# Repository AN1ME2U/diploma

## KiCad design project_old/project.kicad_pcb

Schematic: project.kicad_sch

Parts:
C1, C9, C10, C18, C19, C20, C21, C22, C24, C25, C26, C27, C28, C29, C30: 0.1u; C_0603_1608Metric_Pad1.08x0.95mm_HandSolder
C2, C3, C11, C12: 10u; CP_EIA-6032-15_Kemet-U_Pad2.25x2.35mm_HandSolder
C4, C23: 0.001u; C_0603_1608Metric_Pad1.08x0.95mm_HandSolder
C5, C6, C14, C15: 22u; CP_EIA-6032-15_Kemet-U_Pad2.25x2.35mm_HandSolder
C7, C8, C16, C17: 0.1u; C_0805_2012Metric_Pad1.18x1.45mm_HandSolder
C13: 1u; C_0603_1608Metric_Pad1.08x0.95mm_HandSolder
D1: D; D_0805_2012Metric_Pad1.15x1.40mm_HandSolder
D2: LED; LED_0805_2012Metric_Pad1.15x1.40mm_HandSolder
J1: USB_C_Receptacle_USB2.0; USB_C_Receptacle_HRO_TYPE-C-31-M-12
J2: Conn_01x03; PinHeader_1x03_P2.54mm_Vertical
J3: USB_A; USB_A_Molex_67643_Horizontal
L1, L2, L3, L4: 220; L_2010_5025Metric_Pad1.52x2.65mm_HandSolder
R1, R3, R9: 1M; R_0603_1608Metric_Pad0.98x0.95mm_HandSolder
R2, R4, R5, R6: 4.7k; R_0603_1608Metric_Pad0.98x0.95mm_HandSolder
R7: 9.53; R_0603_1608Metric_Pad0.98x0.95mm_HandSolder
R8: 4K; R_0603_1608Metric_Pad0.98x0.95mm_HandSolder
R10: 24k9; R_0603_1608Metric_Pad0.98x0.95mm_HandSolder
U1: AMS1117-5.0; SOT-223-3_TabPin2
U2, U5: AMS1117-3.3; SOT-223-3_TabPin2
U3, U7: USBLC6-2P6; SOT-666
U4: AMS1117-1.5; SOT-223-3_TabPin2
U6: TUSB4041I; HTQFP-64-1EP_10x10mm_P0.5mm_EP8x8mm_Mask4.4x4.4mm_ThermalVi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
U8: TPS2560; VSON-10-1EP_3x3mm_P0.5mm_EP1.65x2.4mm
Y1: Crystal_GND23; Crystal_SMD_2520-4Pin_2.5x2.0mm

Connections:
1V1_pereph: C24.1, C25.1, C26.1, C27.1, C28.1, C29.1, C30.1, U6.19 (VDD), U6.25 (VDD), U6.37 (VDD), U6.45 (VDD), U6.53 (VDD), U6.60 (VDD), U6.63 (VDD)
1V2_pereph: L3.2
3V3_header: L2.2; also elsewhere on the board
3V3_pereph: C18.1, C19.1, C20.1, C22.1, L4.2, U6.2 (VDD33), U6.20 (VDD33), U6.31 (VDD33), U6.48 (VDD33); also elsewhere on the board
5V_header: L1.2; also elsewhere on the board
+5V: C2.1, C3.1, C11.1, C12.1, D1.1 (K), R8.1, U1.3 (VI), U2.3 (VI), U3.5 (VBUS), U4.3 (VI), U5.3 (VI), U6.16 (USB_VBUS), U8.2 (IN), U8.3 (IN); also elsewhere on the board
/USB_MAIN_N: J1.A7 (D-), J1.B7 (D-), U3.3 (I/O2)
/USB_MAIN_P: J1.A6 (D+), J1.B6 (D+), U3.1 (I/O1)
GND: C1.2, C2.2, C3.2, C4.2, C5.2, C6.2, C7.2, C8.2, C9.2, C10.2, C11.2, C12.2, C13.1, C14.2, C15.2, C16.2, C17.2, C18.2, C19.2, C20.2, C21.2, C22.2, C23.2, C24.2, C25.2, C26.2, C27.2, C28.2, C29.2, C30.2, D2.1 (K), J1.A1 (GND), J1.A12 (GND), J1.B1 (GND), J1.B12 (GND), J3.4 (GND), R1.2, R2.2, R4.2, R5.2, R6.2, R7.2, R9.2, R10.2, U1.1 (GND), U2.1 (GND), U3.2 (GND), U4.1 (GND), U5.1 (GND), U6.65 (VSS), U7.2 (GND), U8.1 (GND), Y1.2, Y1.4; also elsewhere on the board
unnamed: C1.1, C4.1, J1.S1 (SHIELD), R1.1
unnamed: C5.1, C7.1, L1.1, U1.2 (VO)
unnamed: C6.1, C8.1, L2.1, U2.2 (VO)
unnamed: C9.1, R3.1, U6.30 (XI), Y1.1
unnamed: C10.1, R3.2, U6.29 (XO), Y1.3
unnamed: C13.2, U6.18 (GRSTz)
unnamed: C14.1, C16.1, L3.1, U4.2 (VO)
unnamed: C15.1, C17.1, L4.1, U5.2 (VO)
unnamed: C21.1, C23.1, J3.5 (Shield), R9.1
unnamed: D1.2 (A), J1.A4 (VBUS), J1.A9 (VBUS), J1.B4 (VBUS), J1.B9 (VBUS)
unnamed: D2.2 (A), R8.2
unnamed: J2.1, U6.7 (SMBUSz)
unnamed: J2.2, U6.6 (SCL/SMBCLK)
unnamed: J2.3, U6.5 (SDA/SMBDAT)
unnamed: R2.1, U6.10 (GANGED/SMBA2/HS_UP)
unnamed: R4.1, U6.8 (FULLPWRMGMTz/SMBA1)
unnamed: R5.1, U6.13 (AUTOENz/HS_SUSPEND)
unnamed: R6.1, U6.17 (TEST)
unnamed: R7.1, U6.32 (USB_R1)
unnamed: R10.1, U8.7 (ILM)
unnamed: U3.4 (I/O2), U6.22 (USB_DM_UP)
unnamed: U3.6 (I/O1), U6.21 (USB_DP_UP)
USB1_DN: U6.34 (USB_DM_DN1); also elsewhere on the board
USB1_DP: U6.33 (USB_DP_DN1); also elsewhere on the board
USB2_DN: U6.42 (USB_DM_DN2); also elsewhere on the board
USB2_DP: U6.41 (USB_DP_DN2); also elsewhere on the board
USB3_DN: U6.50 (USB_DM_DN3); also elsewhere on the board
USB3_DP: U6.49 (USB_DP_DN3); also elsewhere on the board
USB4_DN: J3.2 (D-), U6.57 (USB_DM_DN4), U7.1 (I/O1), U7.6 (I/O1)
USB4_DP: J3.3 (D+), U6.56 (USB_DP_DN4), U7.3 (I/O2), U7.4 (I/O2)
USB4_VBUS: J3.1 (VBUS), U7.5 (VBUS), U8.9 (OUT1)
USB_OTG_VBUS: U8.8 (OUT2); also elsewhere on the board

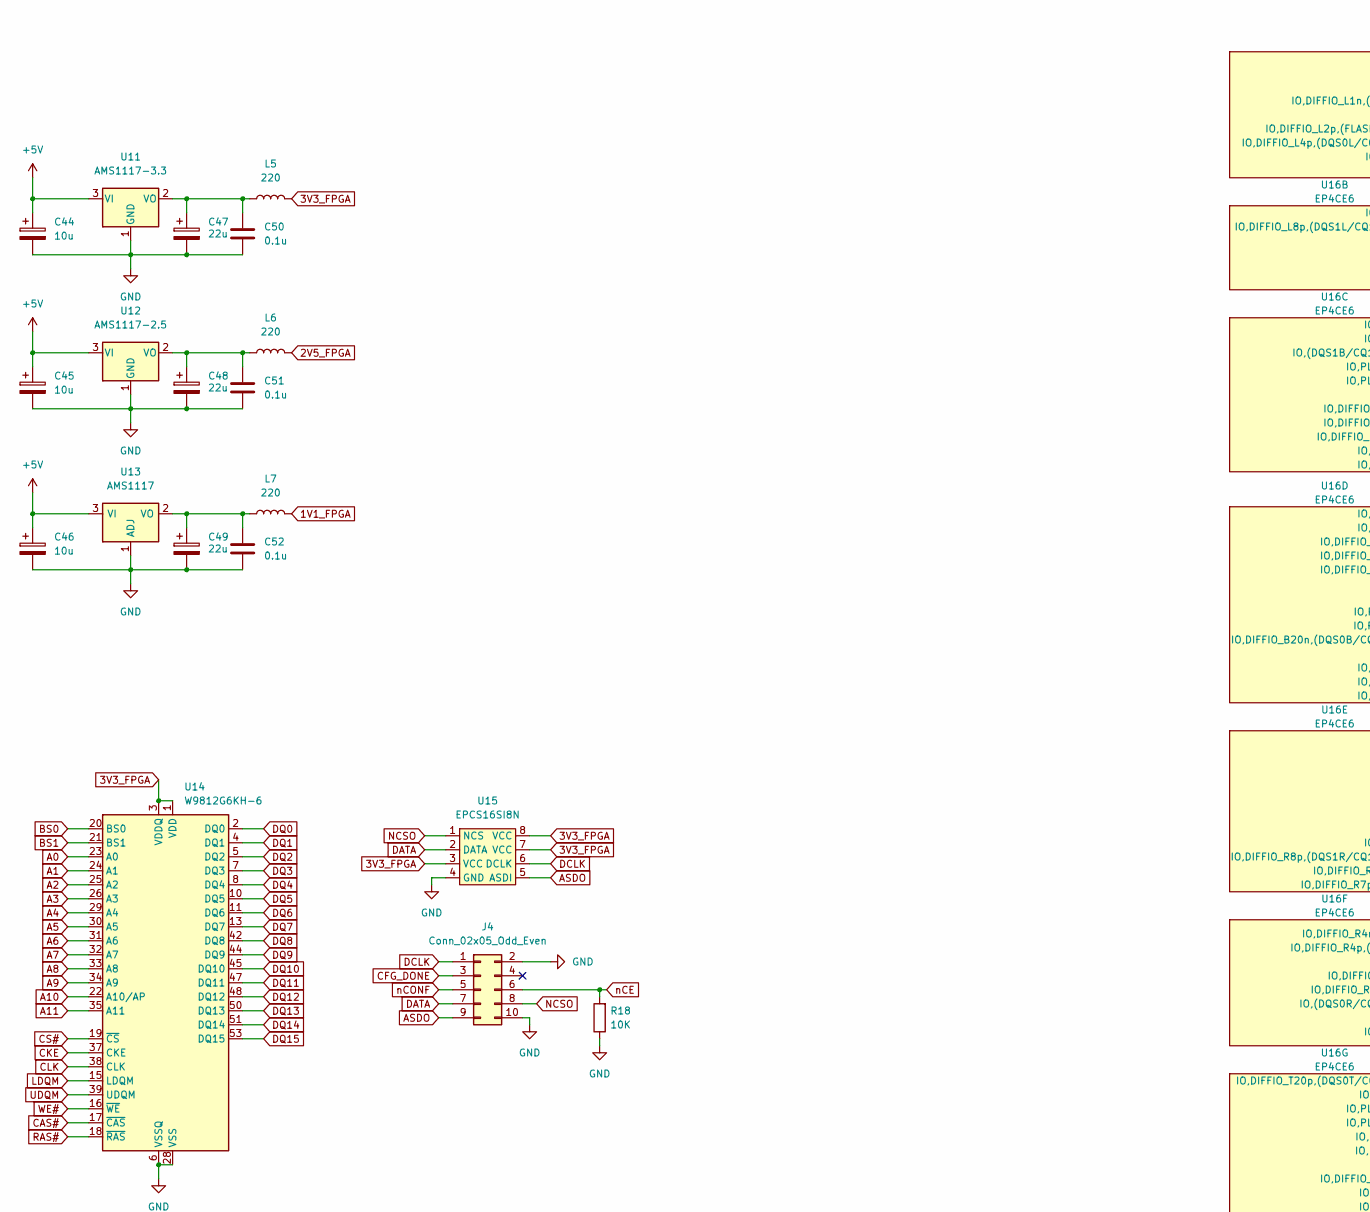
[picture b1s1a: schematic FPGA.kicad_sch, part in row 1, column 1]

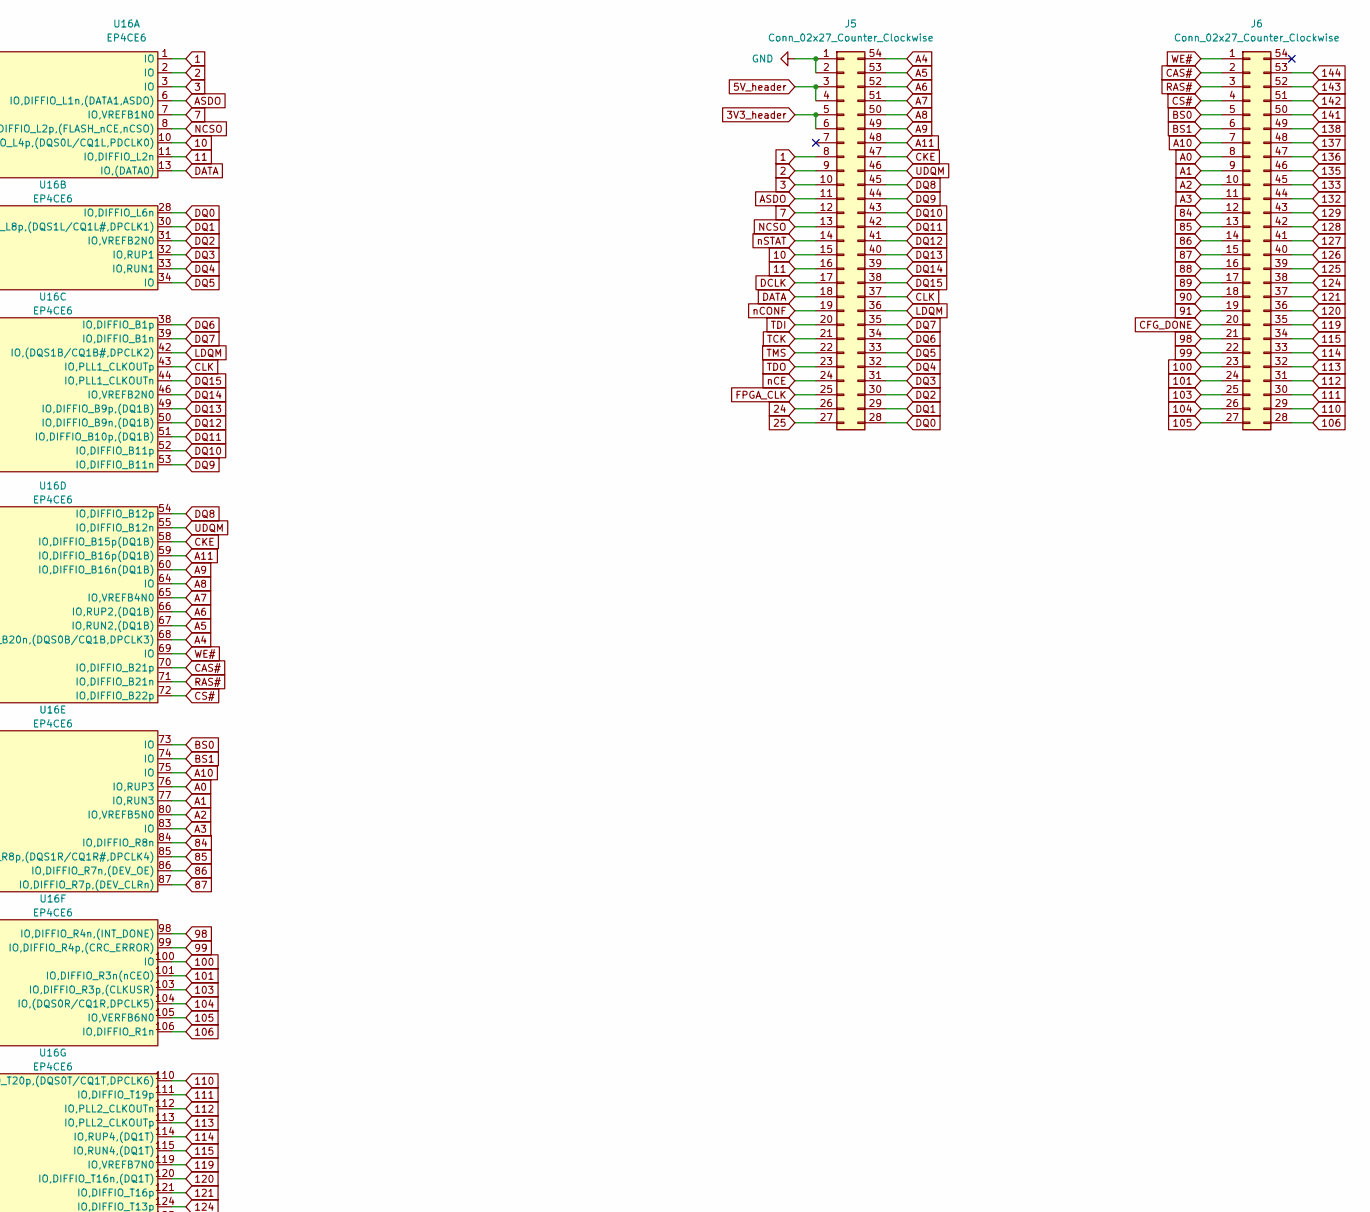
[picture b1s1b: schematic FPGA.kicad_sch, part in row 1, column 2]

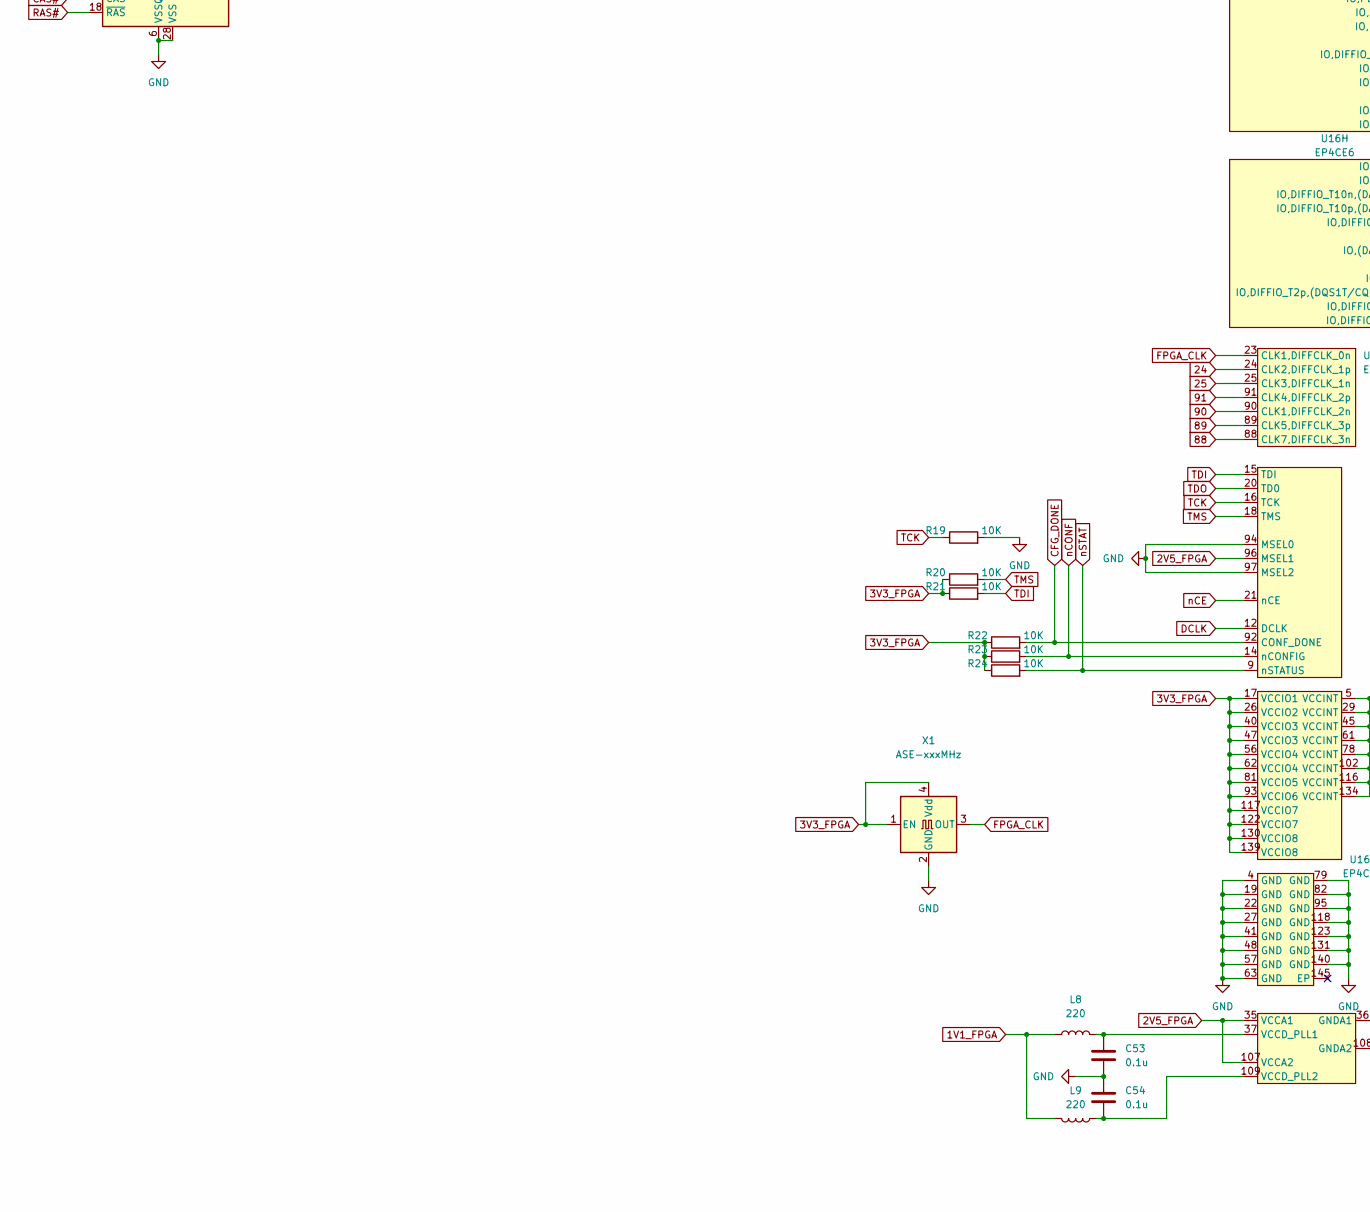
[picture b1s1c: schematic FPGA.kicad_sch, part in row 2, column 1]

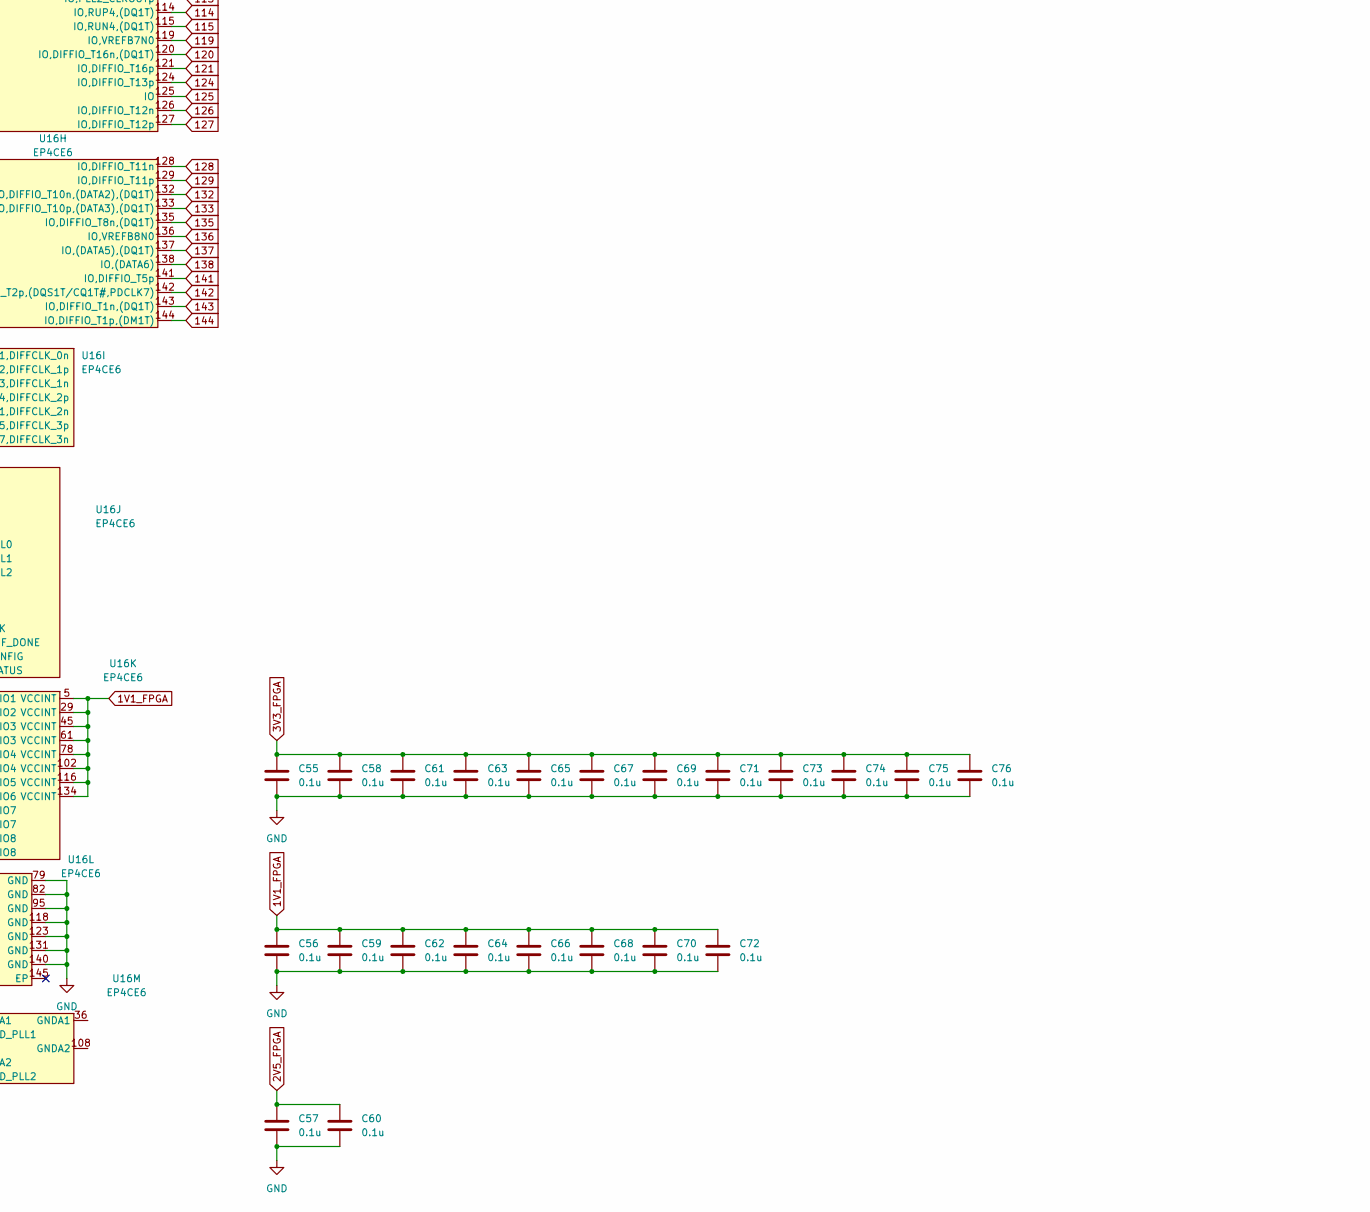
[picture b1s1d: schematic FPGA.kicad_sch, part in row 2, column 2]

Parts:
C44, C45, C46: 10u; CP_EIA-6032-15_Kemet-U_Pad2.25x2.35mm_HandSolder
C47, C48, C49: 22u; CP_EIA-6032-15_Kemet-U_Pad2.25x2.35mm_HandSolder
C50, C51, C52: 0.1u; C_0805_2012Metric_Pad1.18x1.45mm_HandSolder
C53, C54, C55, C56, C57, C58, C59, C60, C61, C62, C63, C64, C65, C66, C67, C68, C69, C70, C71, C72, C73, C74, C75, C76: 0.1u; C_0603_1608Metric_Pad1.08x0.95mm_HandSolder
J4: Conn_02x05_Odd_Even; PinHeader_2x05_P2.54mm_Vertical
J5, J6: Conn_02x27_Counter_Clockwise; PinHeader_2x27_P2.54mm_Vertical
L5, L6, L7, L8, L9: 220; L_2010_5025Metric_Pad1.52x2.65mm_HandSolder
R18, R19, R20, R21, R22, R23, R24: 10K; R_0603_1608Metric_Pad0.98x0.95mm_HandSolder
U11: AMS1117-3.3; SOT-223-3_TabPin2
U12: AMS1117-2.5; SOT-223-3_TabPin2
U13: AMS1117; SOT-223-3_TabPin2
U14: W9812G6KH-6; TSOP-II-54_22.2x10.16mm_P0.8mm
U15: EPCS16SI8N; SOIC-8-1EP_3.9x4.9mm_P1.27mm_EP2.29x3mm
U16: EP4CE6; TQFP-144_20x20mm_P0.5mm
X1: ASE-xxxMHz; Oscillator_SMD_Abracon_ASE-4Pin_3.2x2.5mm

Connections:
1: J5.8, U16.1 (IO)
1V1_FPGA: C56.1, C59.1, C62.1, C64.1, C66.1, C68.1, C70.1, C72.1, L7.2, L8.1, L9.2, U16.5 (VCCINT), U16.29 (VCCINT), U16.45 (VCCINT), U16.61 (VCCINT), U16.78 (VCCINT), U16.102 (VCCINT), U16.116 (VCCINT), U16.134 (VCCINT)
2: J5.9, U16.2 (IO)
2V5_FPGA: C57.1, C60.1, L6.2, U16.35 (VCCA1), U16.96 (MSEL1), U16.107 (VCCA2)
3: J5.10, U16.3 (IO)
3V3_FPGA: C55.1, C58.1, C61.1, C63.1, C65.1, C67.1, C69.1, C71.1, C73.1, C74.1, C75.1, C76.1, L5.2, R20.1, R21.1, R22.1, R23.1, R24.1, U14.1 (VDD), U14.3 (VDDQ), U14.9 (VDDQ), U14.14 (VDD), U14.27 (VDD), U14.43 (VDDQ), U14.49 (VDDQ), U15.3 (VCC), U15.7 (VCC), U15.8 (VCC), U16.17 (VCCIO1), U16.26 (VCCIO2), U16.40 (VCCIO3), U16.47 (VCCIO3), U16.56 (VCCIO4), U16.62 (VCCIO4), U16.81 (VCCIO5), U16.93 (VCCIO6), U16.117 (VCCIO7), U16.122 (VCCIO7), U16.130 (VCCIO8), U16.139 (VCCIO8), X1.1 (EN), X1.4 (Vdd)
3V3_header: J5.5, J5.6; also elsewhere on the board
5V_header: J5.3, J5.4; also elsewhere on the board
7: J5.12, U16.7 (IO,VREFB1N0)
10: J5.15, U16.10 (IO,DIFFIO_L4p,(DQS0L/CQ1L,PDCLK0))
11: J5.16, U16.11 (IO,DIFFIO_L2n)
24: J5.26, U16.24 (CLK2,DIFFCLK_1p)
25: J5.27, U16.25 (CLK3,DIFFCLK_1n)
84: J6.12, U16.84 (IO,DIFFIO_R8n)
85: J6.13, U16.85 (IO,DIFFIO_R8p,(DQS1R/CQ1R#,DPCLK4))
86: J6.14, U16.86 (IO,DIFFIO_R7n,(DEV_OE))
87: J6.15, U16.87 (IO,DIFFIO_R7p,(DEV_CLRn))
88: J6.16, U16.88 (CLK7,DIFFCLK_3n)
89: J6.17, U16.89 (CLK5,DIFFCLK_3p)
90: J6.18, U16.90 (CLK1,DIFFCLK_2n)
91: J6.19, U16.91 (CLK4,DIFFCLK_2p)
98: J6.21, U16.98 (IO,DIFFIO_R4n,(INT_DONE))
99: J6.22, U16.99 (IO,DIFFIO_R4p,(CRC_ERROR))
100: J6.23, U16.100 (IO)
101: J6.24, U16.101 (IO,DIFFIO_R3n(nCEO))
103: J6.25, U16.103 (IO,DIFFIO_R3p,(CLKUSR))
104: J6.26, U16.104 (IO,(DQS0R/CQ1R,DPCLK5))
105: J6.27, U16.105 (IO,VERFB6N0)
106: J6.28, U16.106 (IO,DIFFIO_R1n)
110: J6.29, U16.110 (IO,DIFFIO_T20p,(DQS0T/CQ1T,DPCLK6))
111: J6.30, U16.111 (IO,DIFFIO_T19p)
112: J6.31, U16.112 (IO,PLL2_CLKOUTn)
113: J6.32, U16.113 (IO,PLL2_CLKOUTp)
114: J6.33, U16.114 (IO,RUP4,(DQ1T))
115: J6.34, U16.115 (IO,RUN4,(DQ1T))
119: J6.35, U16.119 (IO,VREFB7N0)
120: J6.36, U16.120 (IO,DIFFIO_T16n,(DQ1T))
121: J6.37, U16.121 (IO,DIFFIO_T16p)
124: J6.38, U16.124 (IO,DIFFIO_T13p)
125: J6.39, U16.125 (IO)
126: J6.40, U16.126 (IO,DIFFIO_T12n)
127: J6.41, U16.127 (IO,DIFFIO_T12p)
128: J6.42, U16.128 (IO,DIFFIO_T11n)
129: J6.43, U16.129 (IO,DIFFIO_T11p)
132: J6.44, U16.132 (IO,DIFFIO_T10n,(DATA2),(DQ1T))
133: J6.45, U16.133 (IO,DIFFIO_T10p,(DATA3),(DQ1T))
135: J6.46, U16.135 (IO,DIFFIO_T8n,(DQ1T))
136: J6.47, U16.136 (IO,VREFB8N0)
137: J6.48, U16.137 (IO,(DATA5),(DQ1T))
138: J6.49, U16.138 (IO,(DATA6))
141: J6.50, U16.141 (IO,DIFFIO_T5p)
142: J6.51, U16.142 (IO,DIFFIO_T2p,(DQS1T/CQ1T#,PDCLK7))
143: J6.52, U16.143 (IO,DIFFIO_T1n,(DQ1T))
144: J6.53, U16.144 (IO,DIFFIO_T1p,(DM1T))
+5V: C44.1, C45.1, C46.1, U11.3 (VI), U12.3 (VI), U13.3 (VI); also elsewhere on the board
A0: J6.8, U14.23 (A0), U16.76 (IO,RUP3)
A1: J6.9, U14.24 (A1), U16.77 (IO,RUN3)
A2: J6.10, U14.25 (A2), U16.80 (IO,VREFB5N0)
A3: J6.11, U14.26 (A3), U16.83 (IO)
A4: J5.54, U14.29 (A4), U16.68 (IO,DIFFIO_B20n,(DQS0B/CQ1B,DPCLK3))
A5: J5.53, U14.30 (A5), U16.67 (IO,RUN2,(DQ1B))
A6: J5.52, U14.31 (A6), U16.66 (IO,RUP2,(DQ1B))
A7: J5.51, U14.32 (A7), U16.65 (IO,VREFB4N0)
A8: J5.50, U14.33 (A8), U16.64 (IO)
A9: J5.49, U14.34 (A9), U16.60 (IO,DIFFIO_B16n(DQ1B))
A10: J6.7, U14.22 (A10/AP), U16.75 (IO)
A11: J5.48, U14.35 (A11), U16.59 (IO,DIFFIO_B16p(DQ1B))
ASDO: J4.9, J5.11, U15.5 (ASDI), U16.6 (IO,DIFFIO_L1n,(DATA1,ASDO))
BS0: J6.5, U14.20 (BS0), U16.73 (IO)
BS1: J6.6, U14.21 (BS1), U16.74 (IO)
CAS#: J6.2, U14.17 (~CAS), U16.70 (IO,DIFFIO_B21p)
CFG_DONE: J4.3, J6.20, R22.2, U16.92 (CONF_DONE)
CKE: J5.47, U14.37 (CKE), U16.58 (IO,DIFFIO_B15p(DQ1B))
CLK: J5.37, U14.38 (CLK), U16.43 (IO,PLL1_CLKOUTp)
CS#: J6.4, U14.19 (~CS), U16.72 (IO,DIFFIO_B22p)
DATA: J4.7, J5.18, U15.2 (DATA), U16.13 (IO,(DATA0))
DCLK: J4.1, J5.17, U15.6 (DCLK), U16.12 (DCLK)
DQ0: J5.28, U14.2 (DQ0), U16.28 (IO,DIFFIO_L6n)
DQ1: J5.29, U14.4 (DQ1), U16.30 (IO,DIFFIO_L8p,(DQS1L/CQ1L#,DPCLK1))
DQ2: J5.30, U14.5 (DQ2), U16.31 (IO,VREFB2N0)
DQ3: J5.31, U14.7 (DQ3), U16.32 (IO,RUP1)
DQ4: J5.32, U14.8 (DQ4), U16.33 (IO,RUN1)
DQ5: J5.33, U14.10 (DQ5), U16.34 (IO)
DQ6: J5.34, U14.11 (DQ6), U16.38 (IO,DIFFIO_B1p)
DQ7: J5.35, U14.13 (DQ7), U16.39 (IO,DIFFIO_B1n)
DQ8: J5.45, U14.42 (DQ8), U16.54 (IO,DIFFIO_B12p)
DQ9: J5.44, U14.44 (DQ9), U16.53 (IO,DIFFIO_B11n)
DQ10: J5.43, U14.45 (DQ10), U16.52 (IO,DIFFIO_B11p)
DQ11: J5.42, U14.47 (DQ11), U16.51 (IO,DIFFIO_B10p,(DQ1B))
DQ12: J5.41, U14.48 (DQ12), U16.50 (IO,DIFFIO_B9n,(DQ1B))
DQ13: J5.40, U14.50 (DQ13), U16.49 (IO,DIFFIO_B9p,(DQ1B))
DQ14: J5.39, U14.51 (DQ14), U16.46 (IO,VREFB2N0)
DQ15: J5.38, U14.53 (DQ15), U16.44 (IO,PLL1_CLKOUTn)
FPGA_CLK: J5.25, U16.23 (CLK1,DIFFCLK_0n), X1.3 (OUT)
GND: C44.2, C45.2, C46.2, C47.2, C48.2, C49.2, C50.2, C51.2, C52.2, C53.2, C54.1, C55.2, C56.2, C57.2, C58.2, C59.2, C60.2, C61.2, C62.2, C63.2, C64.2, C65.2, C66.2, C67.2, C68.2, C69.2, C70.2, C71.2, C72.2, C73.2, C74.2, C75.2, C76.2, J4.2, J4.10, J5.1, J5.2, R18.1, R19.2, U11.1 (GND), U12.1 (GND), U13.1 (ADJ), U14.6 (VSSQ), U14.12 (VSSQ), U14.28 (VSS), U14.41 (VSS), U14.46 (VSSQ), U14.52 (VSSQ), U14.54 (VSS), U15.4 (GND), U16.4 (GND), U16.19 (GND), U16.22 (GND), U16.27 (GND), U16.41 (GND), U16.48 (GND), U16.57 (GND), U16.63 (GND), U16.79 (GND), U16.82 (GND), U16.94 (MSEL0), U16.95 (GND), U16.97 (MSEL2), U16.118 (GND), U16.123 (GND), U16.131 (GND), U16.140 (GND), X1.2 (GND); also elsewhere on the board
LDQM: J5.36, U14.15 (LDQM), U16.42 (IO,(DQS1B/CQ1B#,DPCLK2))
NCSO: J4.8, J5.13, U15.1 (NCS), U16.8 (IO,DIFFIO_L2p,(FLASH_nCE,nCSO))
unnamed: C47.1, C50.1, L5.1, U11.2 (VO)
unnamed: C48.1, C51.1, L6.1, U12.2 (VO)
unnamed: C49.1, C52.1, L7.1, U13.2 (VO)
unnamed: C53.1, L8.2, U16.37 (VCCD_PLL1)
unnamed: C54.2, L9.1, U16.109 (VCCD_PLL2)
RAS#: J6.3, U14.18 (~RAS), U16.71 (IO,DIFFIO_B21n)
TCK: J5.21, R19.1, U16.16 (TCK)
TDI: J5.20, R21.2, U16.15 (TDI)
TDO: J5.23, U16.20 (TD0)
TMS: J5.22, R20.2, U16.18 (TMS)
UDQM: J5.46, U14.39 (UDQM), U16.55 (IO,DIFFIO_B12n)
WE#: J6.1, U14.16 (~WE), U16.69 (IO)
nCE: J4.6, J5.24, R18.2, U16.21 (nCE)
nCONF: J4.5, J5.19, R23.2, U16.14 (nCONFIG)
nSTAT: J5.14, R24.2, U16.9 (nSTATUS)

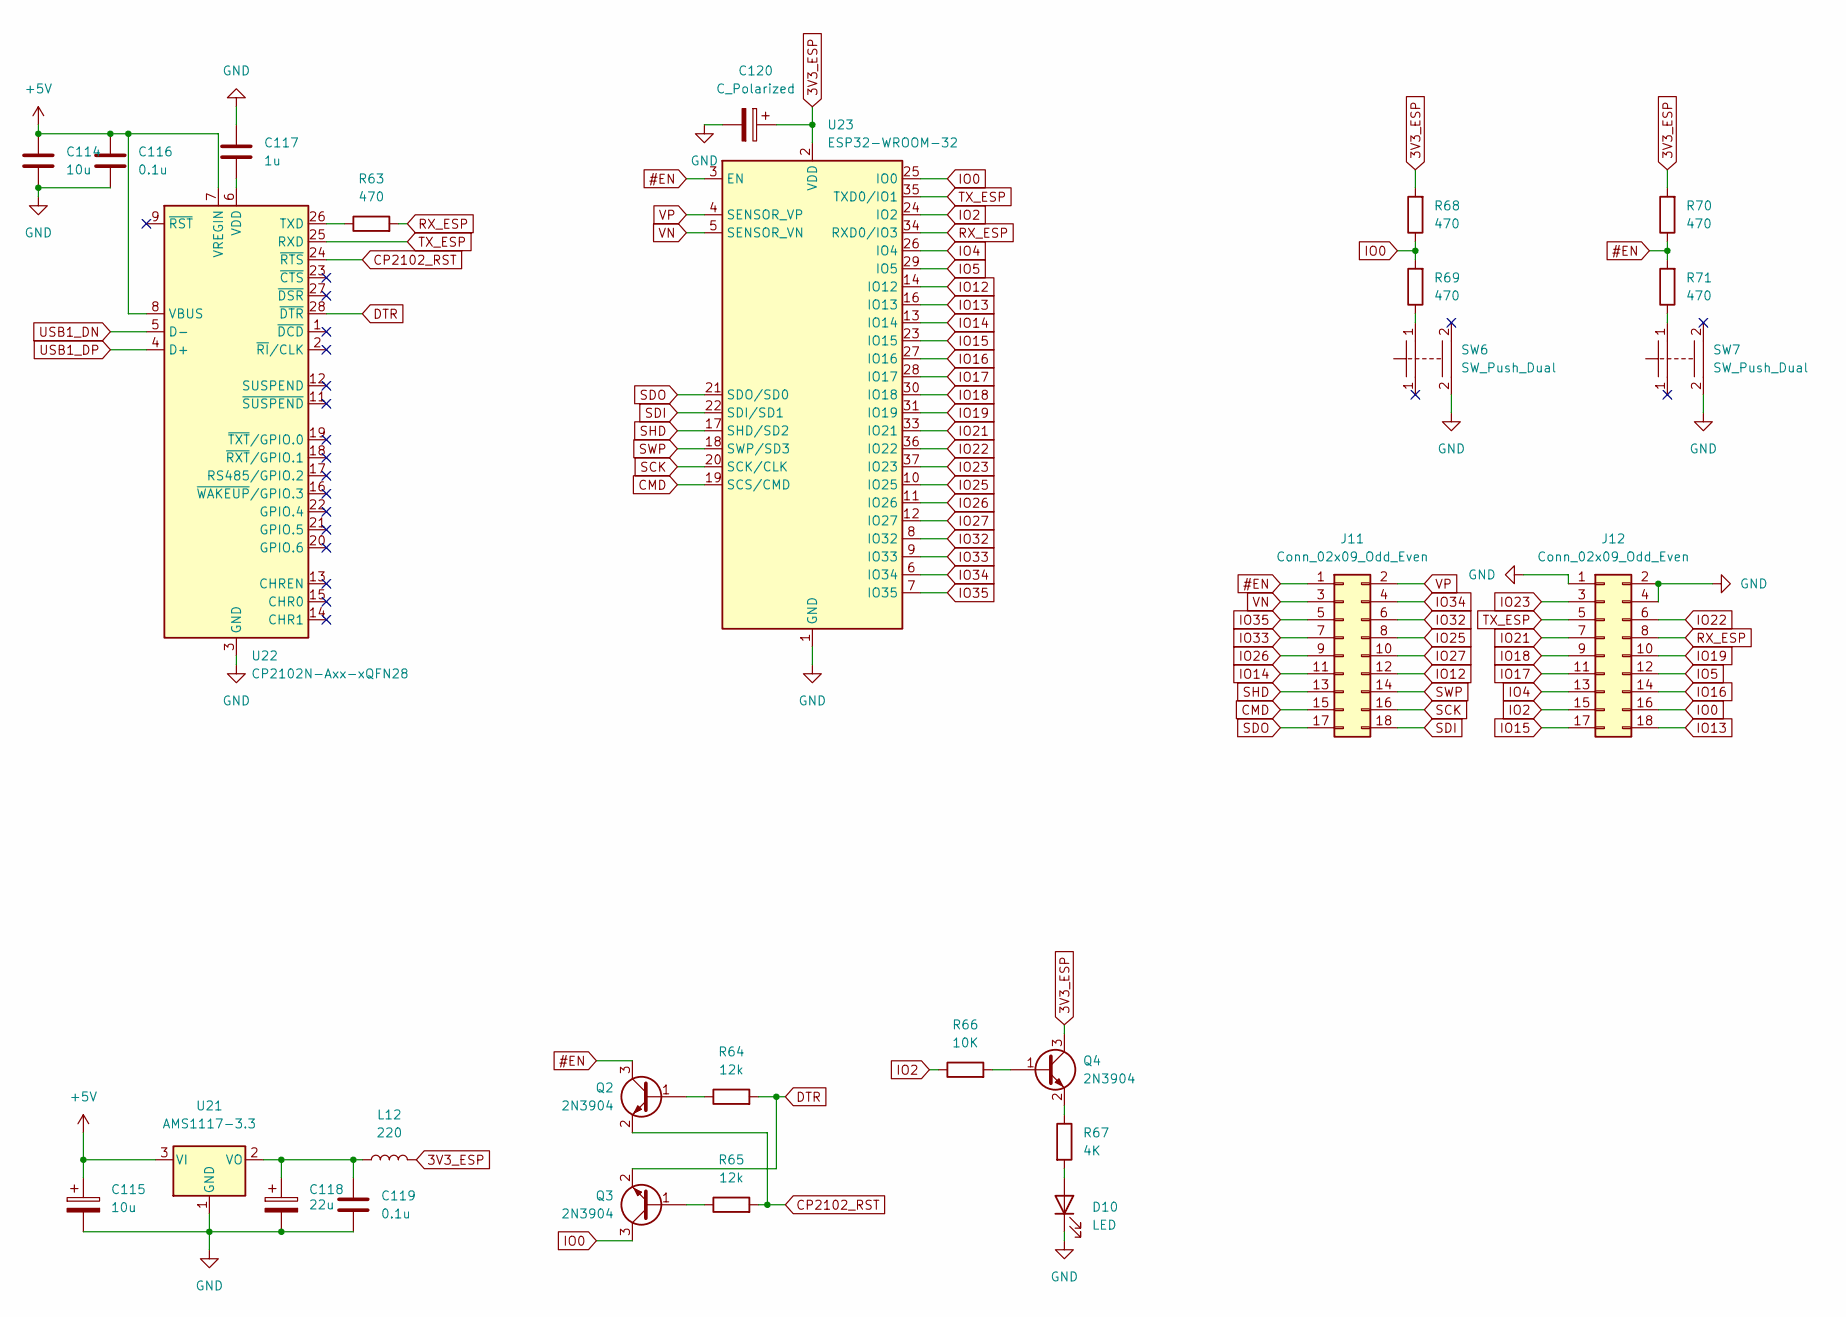
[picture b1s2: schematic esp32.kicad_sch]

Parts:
C114: 10u; C_0603_1608Metric_Pad1.08x0.95mm_HandSolder
C115: 10u; CP_EIA-6032-15_Kemet-U_Pad2.25x2.35mm_HandSolder
C116: 0.1u; C_0603_1608Metric_Pad1.08x0.95mm_HandSolder
C117: 1u; C_0603_1608Metric_Pad1.08x0.95mm_HandSolder
C118: 22u; CP_EIA-6032-15_Kemet-U_Pad2.25x2.35mm_HandSolder
C119: 0.1u; C_0805_2012Metric_Pad1.18x1.45mm_HandSolder
C120: C_Polarized; CP_EIA-1608-08_AVX-J_Pad1.25x1.05mm_HandSolder
D10: LED; LED_0805_2012Metric_Pad1.15x1.40mm_HandSolder
J11, J12: Conn_02x09_Odd_Even; PinSocket_2x09_P2.54mm_Vertical
L12: 220; L_2010_5025Metric_Pad1.52x2.65mm_HandSolder
Q2, Q3, Q4: 2N3904; SOT-23
R63, R68, R69, R70, R71: 470; R_0603_1608Metric_Pad0.98x0.95mm_HandSolder
R64, R65: 12k; R_0603_1608Metric_Pad0.98x0.95mm_HandSolder
R66: 10K; R_0603_1608Metric_Pad0.98x0.95mm_HandSolder
R67: 4K; R_0603_1608Metric_Pad0.98x0.95mm_HandSolder
SW6, SW7: SW_Push_Dual; SW_Push_1P1T_NO_6x6mm_H9.5mm
U21: AMS1117-3.3; SOT-223-3_TabPin2
U22: CP2102N-Axx-xQFN28; QFN-28-1EP_5x5mm_P0.5mm_EP3.35x3.35mm_ThermalVias
U23: ESP32-WROOM-32

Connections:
3V3_ESP: C120.1, L12.2, Q4.3 (C), R68.2, R70.2, U23.2 (VDD)
#EN: J11.1, Q2.3 (C), R70.1, R71.2, U23.3 (EN)
+5V: C114.1, C115.1, C116.1, U21.3 (VI), U22.7 (VREGIN), U22.8 (VBUS); also elsewhere on the board
CMD: J11.15, U23.19 (SCS/CMD)
CP2102_RST: Q2.2 (E), R65.2, U22.24 (~RTS)
DTR: Q3.2 (E), R64.2, U22.28 (~DTR)
GND: C114.2, C115.2, C116.2, C117.1, C118.2, C119.2, C120.2, D10.1 (K), J12.1, J12.2, J12.4, SW6.2, SW7.2, U21.1 (GND), U22.3 (GND), U22.29 (GND), U23.1 (GND), U23.15 (GND), U23.38 (GND), U23.39 (GND); also elsewhere on the board
IO0: J12.16, Q3.3 (C), R68.1, R69.2, U23.25 (IO0)
IO2: J12.15, R66.1, U23.24 (IO2)
IO4: J12.13, U23.26 (IO4)
IO5: J12.12, U23.29 (IO5)
IO12: J11.12, U23.14 (IO12)
IO13: J12.18, U23.16 (IO13)
IO14: J11.11, U23.13 (IO14)
IO15: J12.17, U23.23 (IO15)
IO16: J12.14, U23.27 (IO16)
IO17: J12.11, U23.28 (IO17)
IO18: J12.9, U23.30 (IO18)
IO19: J12.10, U23.31 (IO19)
IO21: J12.7, U23.33 (IO21)
IO22: J12.6, U23.36 (IO22)
IO23: J12.3, U23.37 (IO23)
IO25: J11.8, U23.10 (IO25)
IO26: J11.9, U23.11 (IO26)
IO27: J11.10, U23.12 (IO27)
IO32: J11.6, U23.8 (IO32)
IO33: J11.7, U23.9 (IO33)
IO34: J11.4, U23.6 (IO34)
IO35: J11.5, U23.7 (IO35)
unnamed: C117.2, U22.6 (VDD)
unnamed: C118.1, C119.1, L12.1, U21.2 (VO)
unnamed: D10.2 (A), R67.2
unnamed: Q2.1 (B), R64.1
unnamed: Q3.1 (B), R65.1
unnamed: Q4.1 (B), R66.2
unnamed: Q4.2 (E), R67.1
unnamed: R63.1, U22.26 (TXD)
unnamed: R69.1, SW6.1
unnamed: R71.1, SW7.1
RX_ESP: J12.8, R63.2, U23.34 (RXD0/IO3)
SCK: J11.16, U23.20 (SCK/CLK)
SDI: J11.18, U23.22 (SDI/SD1)
SDO: J11.17, U23.21 (SDO/SD0)
SHD: J11.13, U23.17 (SHD/SD2)
SWP: J11.14, U23.18 (SWP/SD3)
TX_ESP: J12.5, U22.25 (RXD), U23.35 (TXD0/IO1)
USB1_DN: U22.5 (D-); also elsewhere on the board
USB1_DP: U22.4 (D+); also elsewhere on the board
VN: J11.3, U23.5 (SENSOR_VN)
VP: J11.2, U23.4 (SENSOR_VP)

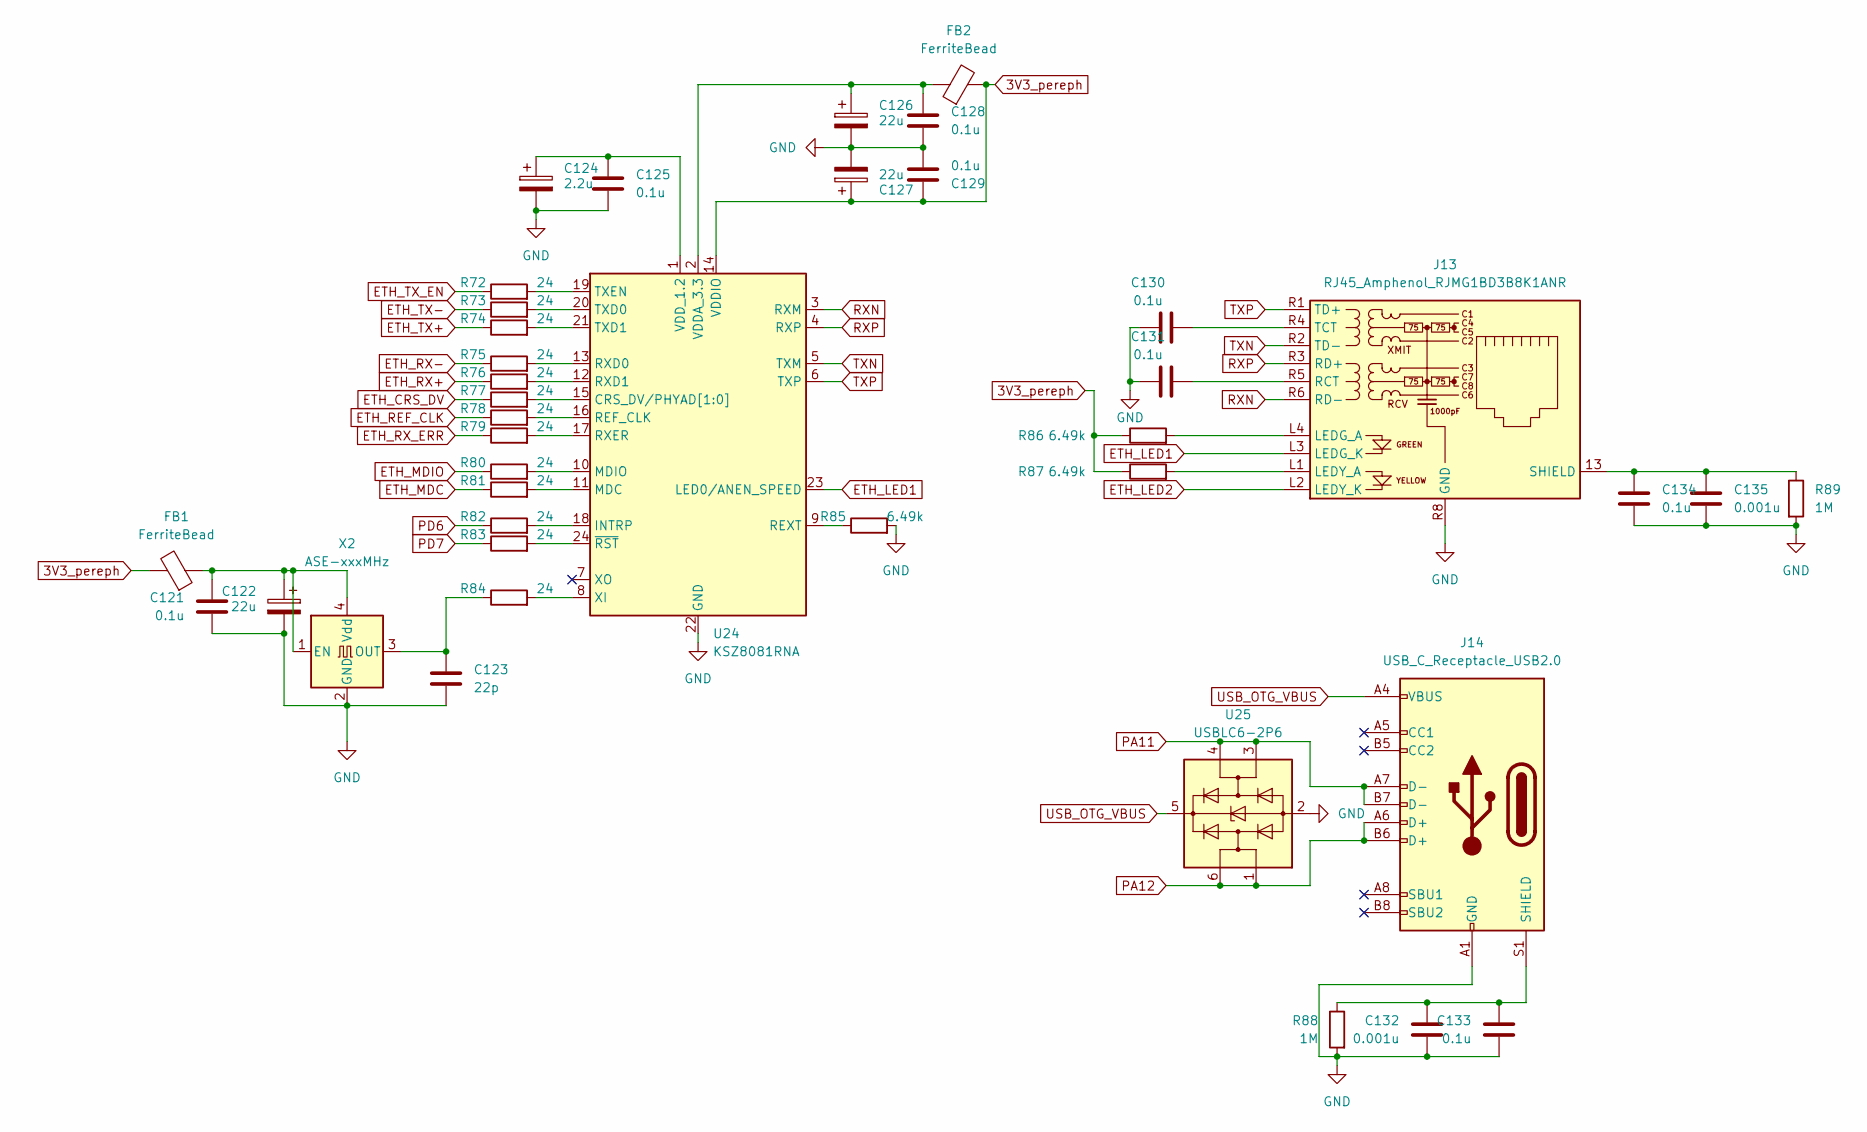
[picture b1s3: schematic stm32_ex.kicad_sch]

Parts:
C121, C125, C128, C129, C130, C131, C133, C134: 0.1u; C_0603_1608Metric_Pad1.08x0.95mm_HandSolder
C122, C126, C127: 22u; CP_EIA-6032-15_Kemet-U_Pad2.25x2.35mm_HandSolder
C123: 22p; C_0603_1608Metric_Pad1.08x0.95mm_HandSolder
C124: 2.2u; CP_EIA-1608-08_AVX-J
C132, C135: 0.001u; C_0603_1608Metric_Pad1.08x0.95mm_HandSolder
FB1, FB2: FerriteBead; L_0805_2012Metric_Pad1.05x1.20mm_HandSolder
J13: RJ45_Amphenol_RJMG1BD3B8K1ANR
J14: USB_C_Receptacle_USB2.0; USB_C_Receptacle_HRO_TYPE-C-31-M-12
R72, R73, R74, R75, R76, R77, R78, R79, R80, R81, R82, R83, R84: 24; R_0603_1608Metric_Pad0.98x0.95mm_HandSolder
R85, R86, R87: 6.49k; R_0603_1608Metric_Pad0.98x0.95mm_HandSolder
R88, R89: 1M; R_0603_1608Metric_Pad0.98x0.95mm_HandSolder
U24: KSZ8081RNA; QFN-24-1EP_4x4mm_P0.5mm_EP2.6x2.6mm_ThermalVias
U25: USBLC6-2P6; SOT-666
X2: ASE-xxxMHz; Oscillator_SMD_Abracon_ASE-4Pin_3.2x2.5mm

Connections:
3V3_pereph: C127.1, C129.1, FB1.2, FB2.2, R86.1, R87.1, U24.14 (VDDIO); also elsewhere on the board
ETH_CRS_DV: R77.1; also elsewhere on the board
ETH_LED1: J13.L3 (LEDG_K), U24.23 (LED0/ANEN_SPEED)
ETH_LED2: J13.L2 (LEDY_K); also elsewhere on the board
ETH_MDC: R81.1; also elsewhere on the board
ETH_MDIO: R80.1; also elsewhere on the board
ETH_REF_CLK: R78.1; also elsewhere on the board
ETH_RX+: R76.1; also elsewhere on the board
ETH_RX-: R75.1; also elsewhere on the board
ETH_RX_ERR: R79.1; also elsewhere on the board
ETH_TX+: R74.1; also elsewhere on the board
ETH_TX-: R73.1; also elsewhere on the board
ETH_TX_EN: R72.1; also elsewhere on the board
GND: C121.2, C122.2, C123.2, C124.2, C125.2, C126.2, C127.2, C128.2, C129.2, C130.1, C131.1, C132.2, C133.2, C134.2, C135.2, J13.R8 (GND), J14.A1 (GND), J14.A12 (GND), J14.B1 (GND), J14.B12 (GND), R85.2, R88.2, R89.2, U24.22 (GND), U24.25 (GND), U25.2 (GND), X2.2 (GND); also elsewhere on the board
unnamed: C123.1, R84.1, X2.3 (OUT)
unnamed: C124.1, C125.1, U24.1 (VDD_1.2)
unnamed: C126.1, C128.1, FB2.1, U24.2 (VDDA_3.3)
unnamed: C130.2, J13.R4 (TCT)
unnamed: C131.2, J13.R5 (RCT)
unnamed: C132.1, C133.1, J14.S1 (SHIELD), R88.1
unnamed: C134.1, C135.1, J13.13 (SHIELD), R89.1
unnamed: J13.L1 (LEDY_A), R87.2
unnamed: J13.L4 (LEDG_A), R86.2
unnamed: R72.2, U24.19 (TXEN)
unnamed: R73.2, U24.20 (TXD0)
unnamed: R74.2, U24.21 (TXD1)
unnamed: R75.2, U24.13 (RXD0)
unnamed: R76.2, U24.12 (RXD1)
unnamed: R77.2, U24.15 (CRS_DV/PHYAD[1:0])
unnamed: R78.2, U24.16 (REF_CLK)
unnamed: R79.2, U24.17 (RXER)
unnamed: R80.2, U24.10 (MDIO)
unnamed: R81.2, U24.11 (MDC)
unnamed: R82.2, U24.18 (INTRP)
unnamed: R83.2, U24.24 (~RST)
unnamed: R84.2, U24.8 (XI)
unnamed: R85.1, U24.9 (REXT)
unnamed: C121.1, C122.1, FB1.1, X2.1 (EN), X2.4 (Vdd)
PA11: J14.A7 (D-), J14.B7 (D-), U25.3 (I/O2), U25.4 (I/O2); also elsewhere on the board
PA12: J14.A6 (D+), J14.B6 (D+), U25.1 (I/O1), U25.6 (I/O1); also elsewhere on the board
PD6: R82.1; also elsewhere on the board
PD7: R83.1; also elsewhere on the board
RXN: J13.R6 (RD-), U24.3 (RXM)
RXP: J13.R3 (RD+), U24.4 (RXP)
TXN: J13.R2 (TD-), U24.5 (TXM)
TXP: J13.R1 (TD+), U24.6 (TXP)
USB_OTG_VBUS: J14.A4 (VBUS), J14.A9 (VBUS), J14.B4 (VBUS), J14.B9 (VBUS), U25.5 (VBUS); also elsewhere on the board
